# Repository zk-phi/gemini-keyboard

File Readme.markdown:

# Gemini keyboard

独自配列、分割40キーの35%キーボードです。

これまでに購入したり設計したりしてきたキーボードたちのアイデアを豊富に盛り込んだ、個人的に集大成のキーボードです。

# 特徴

こんな特徴があります:

キー数

- 数字行から上はバッサリカットして、コンパクトにしています
- 一方で、横方向にはしっかり12列あるので、Ctrl, Shift を一般的な配列と同様に小指に置くことができます。複雑なショートカットキー (Ctrl+Alt+? など) を変わらず使用できます

キー配置

- 左右に割れています
- 両手に b があります
- 横にも縦にもズレた、独特の左右対称配列になっています。横ズレに慣れたタイピングの癖をそこまで矯正することなく、縦ズレのフィット感を享受できます
- 逆に、格子配列や縦ズレに慣れた人にとっては、最上段がホームポジションに近づき押しやすくなります（t, y 遠い問題）
- 親指キーが他のキーから少し離して配置されていて、手を自然に開いた状態で届くようになっています
- スタビライザーが不要です

ケース

- 打鍵感、打鍵音を意識した、独特のアクリル積層ケースになっています
- アクリルなので透明度も高く、LEDの光がよく通ります

その他

- 最大 52 発のフルカラー LED を取り付けられます
- 左右の LED 間は TRRS ケーブルを通して接続されており、オリジナルの発光パターンを比較的簡単に追加できます
- (代償として、 TRS ケーブルでの代用は不可となっています)

# 詳しい設計の経緯
## Matrix-staggered 配列

縦にも横にもズレた Matrix-staggered 配列を採用しています。 Row-staggered で培ったタイピングの癖を無理に矯正することなく、 Columnar-staggered のようなフィット感を実現しようとしました。

横ズレについては、せがたさんの Answer40 で採用された V 字型の Semi-symmetric row-staggered を参考にしています (uniform staggered となっており、若干変わってはいます)。私は b を左右両方の手で打つので、自然に左右に b を置きつつ、指の移動距離を最適化できるこの配列はしっくりきました。またこの配列を採用することで、左右とも自然に縦ズレを両立できています (通常の Row-staggered を採用する Alice などは、右手を折るのに苦労した跡が見られると思います)。分割キーボードなので左右対称だとデザイン的にも良く見えます (ぴったり重ねて収納できるのとか地味に大きいよね)。

縦ズレについては、所有している複数の国産 Columnar-staggered を打ち比べたり、撮影・トレスして俯瞰したりしながら、打鍵感に寄与する要素を考え、落とし所を探りました。分割 Row-staggered キーボードをハの字に置くと、正面から見て、たとえば j と k では k が遠くなります。これを一種の縦ズレととらえると、l, ; を適切に下げることで、 Columnar-staggered として自然なズレ方を実現できます: 右手で例えれば「 j, l あたりを基準として、 k がそれよりも奥にある。逆に ; は手前に来る」感じ。このアイデアをベースに、自分がいいところどりだと感じるズレ具合を、複数回試作して調整しました。

## 少し下がった親指キー

親指キーは他のキーたちより少し下がった位置についています。ふくさんの Claw44 の親指キーの配置が個人的にとても良く、なぜ良いと感じるかを同じく他のレイアウトのトレスと比べながら考えました。その結果「親指の付け根から親指の長さ分進んだところに、円状にキーが配置されていると自然に打てる」(結果だけ見ると当たり前ですが) ということが見えてきたので、この事実と見た目との落とし所として「親指キーを他のキーから少し離した上で (0.2u 分)、1.75u - 1.25u に分割して使う」に至りました。親指キーを3キー設けるパターンも検討してはいたのですが、3キー目は結構無理しないと押せなかったので、それよりは1キーの幅を広く取って個々人のスイートスポットで押しやすくなっている方が良いかな、という判断が含まれています。長めのキーを押した時のカポッて感じの音も好きです。

## 積層ケース

前作でも試した「ピチピチ積層ケース」のアイデアをベースに、自分好みの音・打鍵感になるようチューニングしました。ケースの中間層をただの外枠にするのでなく、部品と干渉するところだけに穴を開けて残り部分にはアクリルを行き渡らせることでケースの密度を上げ、質量を稼ぎつつ音の響く空間の広さを削減しています。

アクリルプレートによるプレートマウントですが、基板内部にスペーサーを立てる一般的なサンドイッチと比較して、プレートがケースの外周全体で支えられるので剛性感はやや高いと思います。とはいえ金属プレートほどでもないので、個人的にはちょうど良いです。

また透明度が高いため LED との相性も良いです。

# ビルドガイド
## パーツ

- Gemini Kit 両手分 (この順に重ねて梱包されています)
  - トップフレーム厚 (3mm, 縁を盛るだけの飾り)
  - トップフレーム薄 (2mm, 厚さが違う以外同じ)
  - トッププレート (3mm, 四角い穴がたくさん)
  - ローワートッププレート (2mm, さらに穴がちょっと多い)
  - ミドルフレーム (2mm, 上下に分断されている)
  - 基板 (左右の別があるので注意)
  - ローワーミドルフレーム (3mm, 不思議な形の穴がたくさん, 左右の別あり)
  - ボトムプレート (3mm, promicro / trrs の通る空間が空けてある)
  - 底板２枚 (2mm, ネジ穴のみ)

- Gemini Kit 予備パーツ
  - ローワーミドルフレーム薄 (2mm)
  - 追加のトップフレーム厚 (3mm)

- 購入が必要なもの 両手分
  - MX 互換キースイッチ x40
  - ダイオード 1N4148w x40
  - TRRS ジャック MJ-4PP-9 x2
  - 2 ピンタクトスイッチ x2
  - コンスルー付き ProMicro x2 セット
  - LED SK6812mini x52 (任意, 半田付け難易度高めなので注意)
  - M2 ネジ 20mm とナット x 20
  - クッションゴム x 適宜

## ケースのカスタマイズについて

予備パーツを使ってケースの構成を若干カスタマイズできます。

- 底板を省略すると打面の高さを 2mm 下げることができます。一部の部品がむき出しになってしまいますが、気にしないのであればおすすめです

- コンスルーの足を切ると、ローワーミドルフレームを予備パーツの薄い方に交換して打面の高さを 1mm 下げることができます。 TRRS ケーブルを差し込む穴が狭くなるので、プラグの形状によっては干渉する場合がありますが、限界の薄さを狙いたい場合は試す価値ありです

- 打面を下げるカスタマイズをするとネジの長さが余るので、適宜予備のトップフレームを追加していい感じにしてください。トップフレームは厚いほど個人的にはかっこいいと思います

- 打面を下げるカスタマイズをしない場合でも、長めのネジを使うことでトップフレームを追加できます。これもおすすめですが、ちょうどいい長さのネジがなかなか手に入らないのでいろいろ頑張る必要があります（私はニッパでぶった切って錬成しました）

## 組み立て
### Pro Micro の用意

もげ対策、ファームの書き込み、コンスルーの取り付けなどを済ませておきます。

ファームは私の fork に push しておきます。

https://github.com/zk-phi/qmk_firmware

: make gemini:phi:avrdude

コンスルーの向きは Helix などと同様です (https://github.com/MakotoKurauchi/helix/blob/master/Doc/buildguide_jp.md#pro-micro)。

### TRRS ジャック、 LED の実装

LED を取り付ける場合、左手側の基板から先に取り付けてゆきます。コの字の印のあるところが LED の VCC になります。 LED の順序は次のようになっています：

1. 左手のバックライト（穴に落として背面実装するもの） … Pro Micro に近い側の、一番上のキー（表から見ると左上）から横方向に進み、端まで来たら次の行の Pro Micro に近い側に戻る (Z 字)

2. 左手のアンダーグロー（通常の表面実装） … Pro Micro に近い側の、上側から同様の順

失敗しやすいので、 Pro Micro を接続して都度点灯確認をするのがおすすめです。左手が動作確認できたら右手も同様に実装してゆきますが、今回の基板では右手の LED も左手の Pro Micro で制御するので、右手の点灯確認には TRRS ケーブルでの接続が必要です。右手の LED も同様に Pro Micro に近い側から実装してゆきます。

### ダイオード、リセットスイッチの実装

ダイオードはコの字の印がカソード側（ダイオードの目印のついている側）です。実装できたら Pro Micro を接続し、ピンセットなどでスイッチの足をショートさせて、ちゃんとキー入力が行われるか動作確認しておくのがおすすめです。

### スイッチの実装

スイッチを半田付けしてしまうと、全てのスイッチをはがさない限りプレートを外すことができなくなります。ここまでの動作確認ができていない場合は、動作確認してからスイッチにとりかかることを強く勧めます。

Pro Micro を外し、スイッチを実装します。基板にローワートッププレート、トッププレートをこの順に重ね、スイッチを奥まではめ込み、裏から半田付けします。 Pro Micro の裏にくるスイッチの足はカットする必要がある場合があります（Pro Micro の個体によってはそのままでも大丈夫な場合があるので、確認するのがおすすめです）。基板の収まる空間は高さ 2mm しか取られていません。基板自体の厚みが 1.6mm あるので、基板が 0.4mm 以上浮いてついてしまっていると干渉します。スイッチをしっかり押し込み、プレートを基板にぴったりくっつけた状態で半田付けするように注意してください。

スイッチの実装が終わったらまた Pro Micro を刺しておきます。

### ケースを組み立てる

下から

- 底板
- ボトムプレート
- ローワーミドルフレーム
- ミドルフレーム
- 実装済みの基板＆トッププレート
- 好みの枚数のトップフレーム

をこの順に重ね、ネジで貫通・ナットで留めます。ローワーミドルフレームには左右の別があるので注意してください。部品に干渉していなければ ok です。

仕上げにクッションゴムを貼り付ければ完成です。

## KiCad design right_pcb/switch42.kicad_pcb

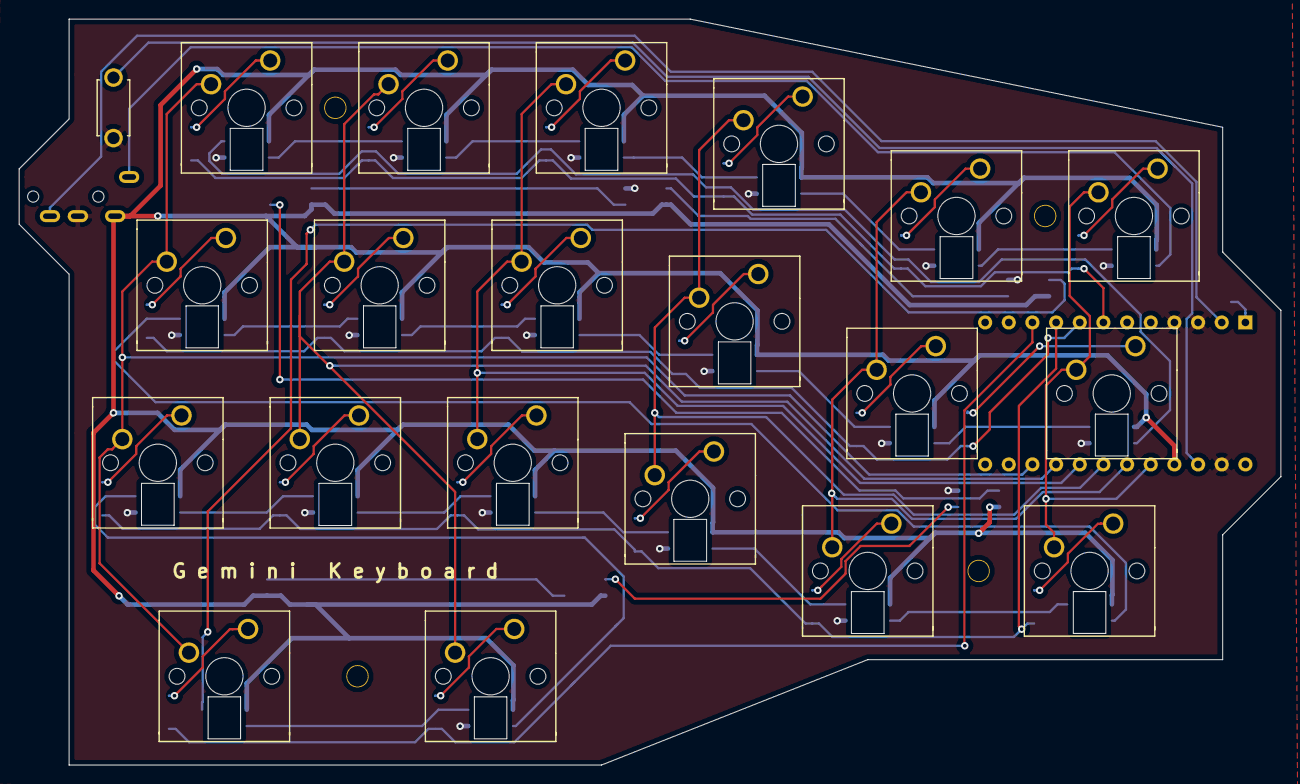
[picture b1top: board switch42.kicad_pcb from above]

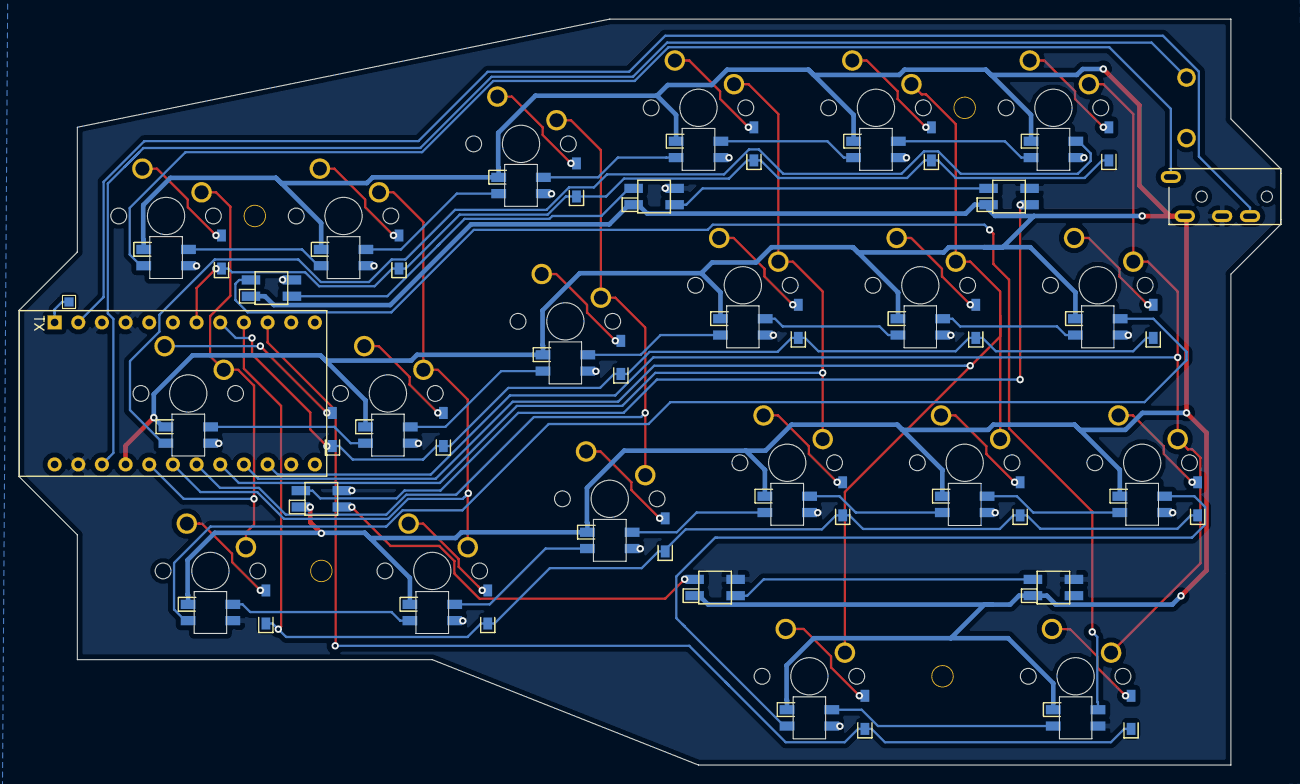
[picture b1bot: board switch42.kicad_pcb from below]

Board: 2 copper layers, 135.4 x 80.1 mm, 73 parts (28 on the bottom side), 60 nets.

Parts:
D1, D2, D3, D4, D5, D6, D7, D8, D9, D10, D11, D12, D14, D15, D16, D17, D18, D19, D20, D21: D; D_SMD-irreversible
J1: MJ-4PP-9; MJ-4PP-9-irreversible
L1, L2, L3, L4, L5, L6, L7, L8, L9, L10, L11, L12, L14, L15, L16, L17, L18, L19, L20, L21: SK6812MINI; SK6812MINI-irreversible
L22, L23, L24, L25, L26, L27: SK6812MINI; SK6812MINI-underglow-irreversible
Ref**: Val**; M2_SCREW_HOLE
Ref**#2, Ref**#3, Ref**#4: Val**; M2_SCREW_HOLE
SW1: SW_PUSH; ResetSW-irreversible
SW2, SW5, SW6, SW7, SW8, SW9, SW10, SW11, SW12, SW13, SW15, SW16, SW17, SW19, SW20, SW21: SW_PUSH; MX_1.00u-irreversible
SW3, SW18: SW_PUSH; MX_1.25u-irreversible
SW4: SW_PUSH; MX_1.50u-irreversible
SW22: SW_PUSH; MX_1.75u-irreversible
U1: ProMicro; ProMicro_Reversed_Conthrough-irreversible

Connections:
GND: J1.C, L1.2, L2.2, L3.2, L4.2, L5.2, L6.2, L7.2, L8.2, L9.2, L10.2, L11.2, L12.2, L14.2, L15.2, L16.2, L17.2, L18.2, L19.2, L20.2, L21.2, L22.2, L23.2, L24.2, L25.2, L26.2, L27.2, SW1.2, U1.3, U1.4, U1.23
unnamed: D1.2, SW2.2
unnamed: D2.2, SW3.2
unnamed: D3.2, SW4.2
unnamed: D4.2, SW5.2
unnamed: D5.2, SW6.2
unnamed: D6.2, SW7.2
unnamed: D7.2, SW8.2
unnamed: D8.2, SW9.2
unnamed: D9.2, SW10.2
unnamed: D10.2, SW11.2
unnamed: D11.2, SW12.2
unnamed: D12.2, SW13.2
unnamed: D14.2, SW15.2
unnamed: D15.2, SW16.2
unnamed: D16.2, SW17.2
unnamed: D17.2, SW18.2
unnamed: D18.2, SW19.2
unnamed: D19.2, SW20.2
unnamed: D20.2, SW21.2
unnamed: D21.2, SW22.2
unnamed: L1.1, L4.3
unnamed: L2.1, L5.3
unnamed: L3.1, L6.3
unnamed: L4.1, L7.3
unnamed: L5.1, L8.3
unnamed: L6.1, L9.3
unnamed: L10.1, L14.3
unnamed: L7.1, L10.3
unnamed: L11.1, L15.3
unnamed: L8.1, L11.3
unnamed: L12.1, L16.3
unnamed: L9.1, L12.3
unnamed: L14.1, L18.3
unnamed: L15.1, L19.3
unnamed: L16.1, L20.3
unnamed: L17.1, L21.3
unnamed: L17.3, L20.1
unnamed: L2.3, L18.1
unnamed: L3.3, L19.1
unnamed: L22.1, L23.3
unnamed: L23.1, L24.3
unnamed: L24.1, L25.3
unnamed: L25.1, L26.3
unnamed: L26.1, L27.3
VCC: J1.D, L1.4, L2.4, L3.4, L4.4, L5.4, L6.4, L7.4, L8.4, L9.4, L10.4, L11.4, L12.4, L14.4, L15.4, L16.4, L17.4, L18.4, L19.4, L20.4, L21.4, L22.4, L23.4, L24.4, L25.4, L26.4, L27.4, U1.21
col0: SW2.1, SW3.1, SW4.1, U1.20
col1: SW5.1, SW6.1, SW7.1, U1.19
col2: SW8.1, SW9.1, SW10.1, U1.18
col3: SW11.1, SW12.1, SW13.1, U1.17
col4: SW15.1, SW16.1, SW17.1, SW18.1, U1.16
col5: SW19.1, SW20.1, SW21.1, SW22.1, U1.15
data: J1.B, U1.2
ledin: J1.A, L1.3
reset: SW1.1, U1.22
row0: D1.1, D4.1, D7.1, D10.1, D14.1, D18.1, U1.7
row1: D2.1, D5.1, D8.1, D11.1, D15.1, D19.1, U1.8
row2: D3.1, D6.1, D9.1, D12.1, D16.1, D20.1, U1.9
row3: D17.1, D21.1, U1.10
underglow: L21.1, L22.3

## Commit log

2019-11-28 More images
2019-12-16 Minor updates
2020-08-25 Add PCB
2020-08-25 Add LICENSE
2023-02-19 Replace image
